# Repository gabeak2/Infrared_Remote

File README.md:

# Infrared_Remote
Infrared Remote used to control Nikon DSLRs.  Used an ATTINY412 with MEGATINYCORE.

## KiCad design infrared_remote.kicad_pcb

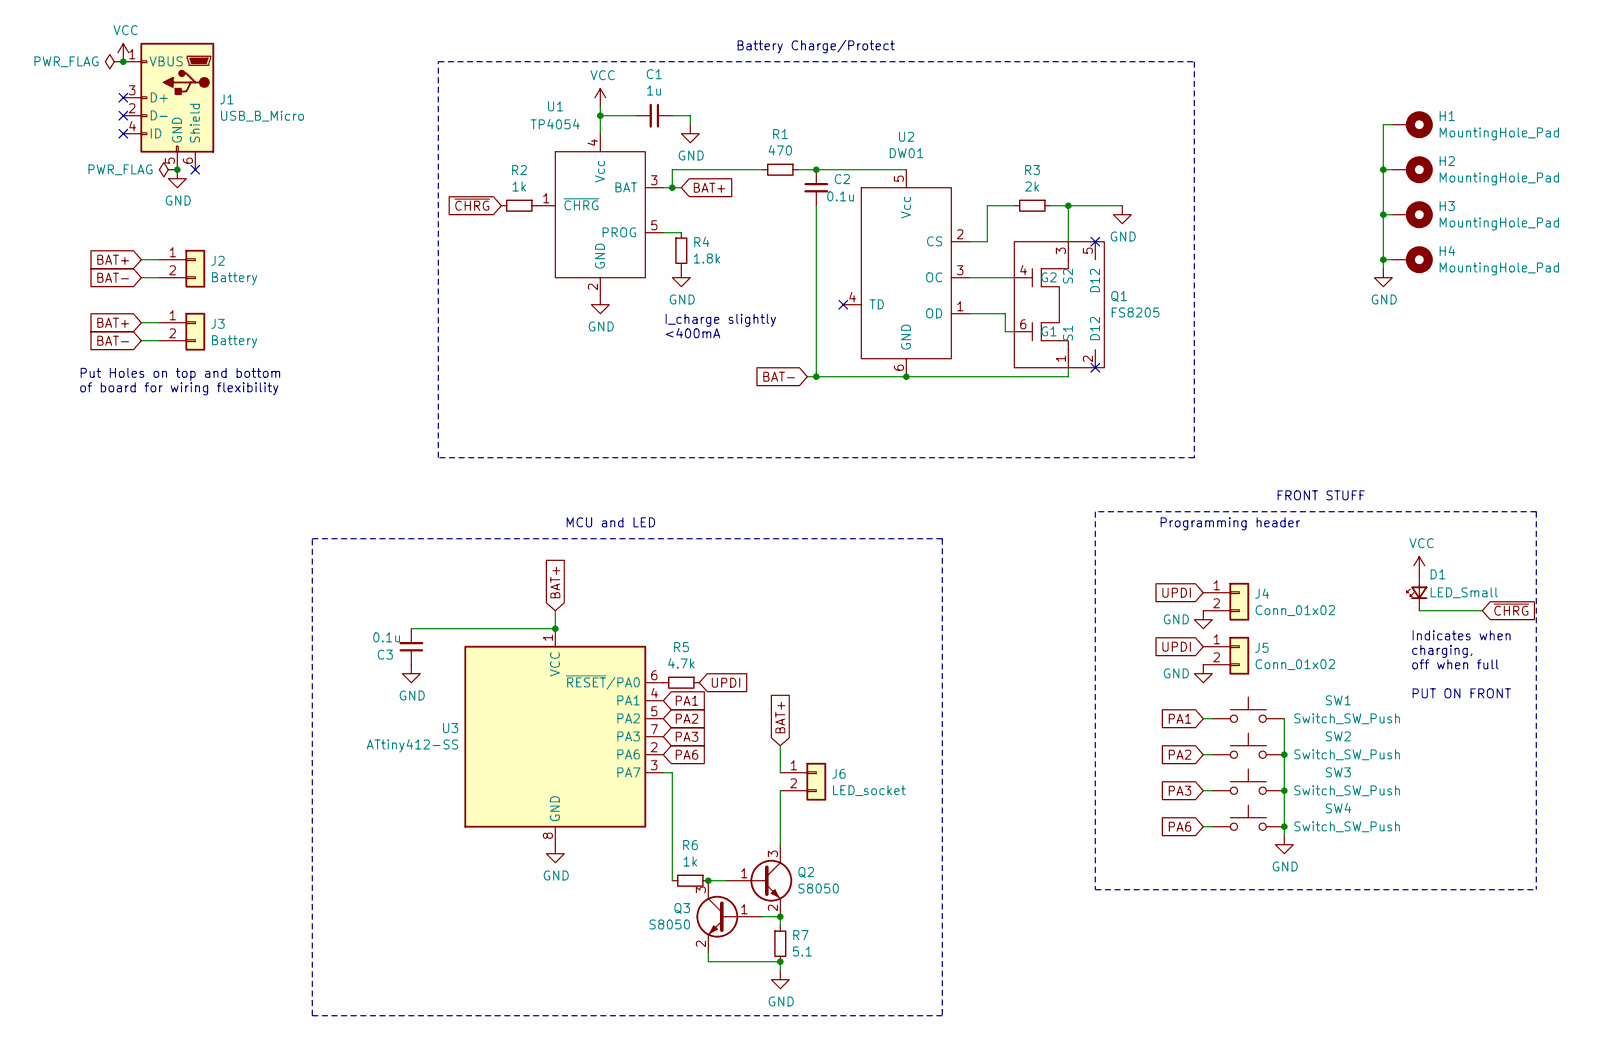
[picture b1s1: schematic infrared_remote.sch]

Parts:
C1: 1u; C_0805_2012Metric_Pad1.15x1.40mm_HandSolder
C2, C3: 0.1u; C_0805_2012Metric_Pad1.15x1.40mm_HandSolder
D1: LED_Small; LED_0805_2012Metric_Pad1.15x1.40mm_HandSolder
H1, H2, H3, H4: MountingHole_Pad; MountingHole_2.2mm_M2_Pad_Via
J1: USB_B_Micro; USB_Micro-B_Molex-105017-0001
J2, J3: Battery; PinSocket_1x02_P2.54mm_Vertical
J4, J5: Conn_01x02; PinSocket_1x02_P2.54mm_Vertical
J6: LED_socket; PinSocket_1x02_P2.54mm_Vertical
Q1: FS8205; SOT-23-6
Q2, Q3: S8050; SOT-23
R1: 470; R_0805_2012Metric
R2, R6: 1k; R_0805_2012Metric
R3: 2k; R_0805_2012Metric
R4: 1.8k; R_0805_2012Metric
R5: 4.7k; R_0805_2012Metric
R7: 5.1; R_0805_2012Metric
SW1, SW2, SW3, SW4: Switch_SW_Push; button_cheapo_ebay_smd
U1: TP4054; SOT-23-5
U2: DW01; SOT-23-6
U3: ATtiny412-SS; SOIC-8_3.9x4.9mm_P1.27mm

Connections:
BAT+: C3.2, J2.1, J3.1, J6.1, R1.2, U1.3 (BAT), U3.1 (VCC)
BAT-: C2.2, J2.2, J3.2, Q1.1 (S1), U2.6 (GND)
GND: C1.1, C3.1, H1.1, H2.1, H3.1, H4.1, J1.5 (GND), J4.2, J5.2, Q1.3 (S2), Q3.2 (E), R3.1, R4.2, R7.2, SW1.2, SW2.2, SW3.2, SW4.2, U1.2 (GND), U3.8 (GND)
unnamed: C2.1, R1.1, U2.5 (Vcc)
unnamed: J6.2, Q2.3 (C)
unnamed: Q1.4 (G2), U2.3 (OC)
unnamed: Q1.6 (G1), U2.1 (OD)
unnamed: Q2.1 (B), Q3.3 (C), R6.1
unnamed: Q2.2 (E), Q3.1 (B), R7.1
unnamed: R2.1, U1.1 (~CHRG)
unnamed: R3.2, U2.2 (CS)
unnamed: R4.1, U1.5 (PROG)
unnamed: R5.2, U3.6 (~RESET~/PA0)
unnamed: R6.2, U3.3 (PA7)
PA1: SW1.1, U3.4 (PA1)
PA2: SW2.1, U3.5 (PA2)
PA3: SW3.1, U3.7 (PA3)
PA6: SW4.1, U3.2 (PA6)
UPDI: J4.1, J5.1, R5.1
VCC: C1.2, D1.2 (A), J1.1 (VBUS), U1.4 (Vcc)
~CHRG: D1.1 (K), R2.2

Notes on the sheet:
Battery Charge/Protect
I_charge slightly <400mA
Put Holes on top and bottom of board for wiring flexibility
Programming header
Indicates when charging, off when full PUT ON FRONT
FRONT STUFF
MCU and LED

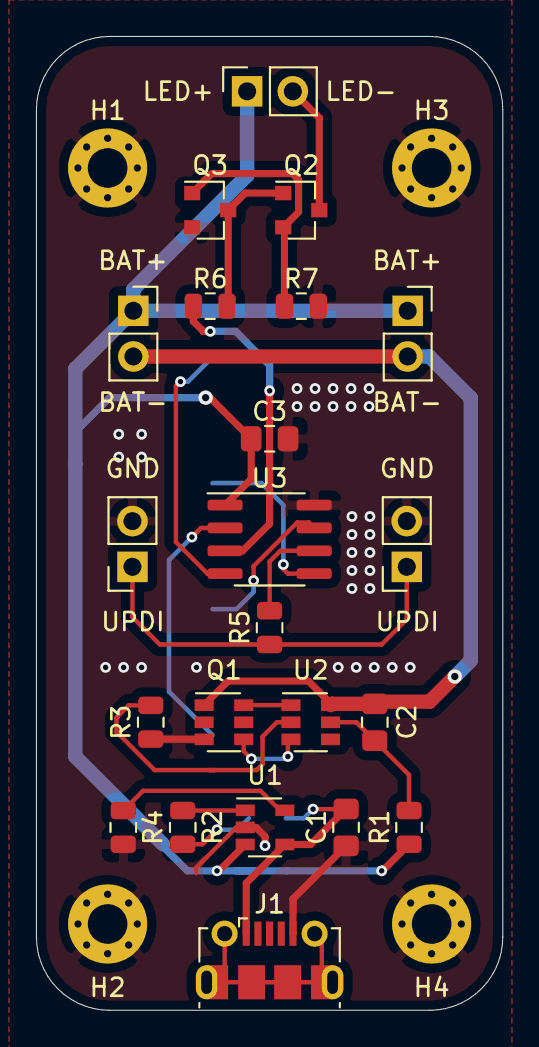
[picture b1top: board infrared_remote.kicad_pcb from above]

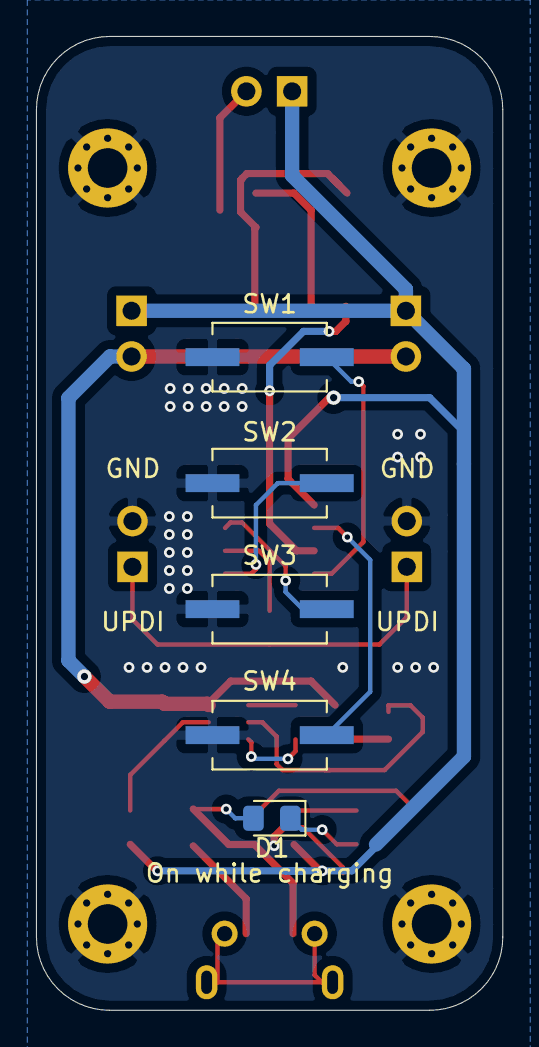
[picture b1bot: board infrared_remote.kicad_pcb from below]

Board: 2 copper layers, 25.9 x 54.1 mm, 31 parts (5 on the bottom side), 21 nets.

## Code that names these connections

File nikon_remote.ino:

#include <avr/sleep.h>

unsigned long prevMicros;
unsigned long prevMillis;

void oscillate();
void nec_oscillate();
void remote_routine();

void setup() {
  prevMillis = millis();
  delay(1000);
  set_sleep_mode(SLEEP_MODE_PWR_DOWN); //super deep sleep
  sleep_enable(); //enable sleep mode
  pinMode(1,OUTPUT); //LED, PA7
  pinMode(2,INPUT_PULLUP); //sw1 PA1
  PORTA.PIN1CTRL |= 0x03; //falling edge when button is pushed
  pinMode(3,INPUT_PULLUP); //sw2 PA2
  PORTA.PIN2CTRL |= 0x03; //falling edge when button is pushed
  pinMode(4,INPUT_PULLUP); //sw3 PA3
  PORTA.PIN3CTRL |= 0x03; //falling edge when button is pushed
  pinMode(0,INPUT_PULLUP); //sw4 PA6
  PORTA.PIN6CTRL |= 0x03; //falling edge when button is pushed
  
}

ISR(PORTA_PORT_vect){ //pin interrupt for all 4 switches
  byte flags = PORTA.INTFLAGS;
  PORTA.INTFLAGS = flags; //clear interrupt flag
}

void loop() {
    sleep_cpu(); //will wake up with interrupt
    remote_routine();
    delay(63);
    remote_routine();
    delay(100); //2 delays together serve as debounce
    digitalWrite(1,LOW);
}

void oscillate(){
  //oscillate pin 1 at the right frequency and duty cycle
  PORTA.OUT |= B10000000; //pin 1 is PA7 -> pin 1 high
  delayMicroseconds(16);
  PORTA.OUT &= B01111111; //pin 1 low
  delayMicroseconds(10);
}

void nec_oscillate(){ //50% duty cycle, 38khz
  prevMicros = micros();
  PORTA.OUT |= B10000000; //pin 1 is PA7 -> pin 1 high
  while( (micros() - prevMicros) < 13);

  prevMicros = micros();
  PORTA.OUT &= B01111111; //pin 1 low
  while( (micros() - prevMicros) < 13);
  
}

//void write_nec_byte(uint8_t bite){
//  
//}

void remote_routine(){

  prevMicros = micros();
  while( (micros() - prevMicros) < 2000){ //2ms high
    oscillate();
  }
  prevMicros = micros();
  while( (micros() - prevMicros) < 27800){ //27.8ms low
    ; //nothing
  }
  prevMicros = micros();
  while( (micros() - prevMicros) < 500){ //27.8ms low
    oscillate();  
  }
  prevMicros = micros();
  while( (micros() - prevMicros) < 1500){ //27.8ms low
    ;  //nothing 
  }
  prevMicros = micros();
  while( (micros() - prevMicros) < 500){ //27.8ms low
    oscillate();  
  }
  prevMicros = micros();
  while( (micros() - prevMicros) < 3500){ //27.8ms low
    ;  //nothing 
  }
  prevMicros = micros();
  while( (micros() - prevMicros) < 500){ //27.8ms low
    oscillate();  
  }
  
    
}
